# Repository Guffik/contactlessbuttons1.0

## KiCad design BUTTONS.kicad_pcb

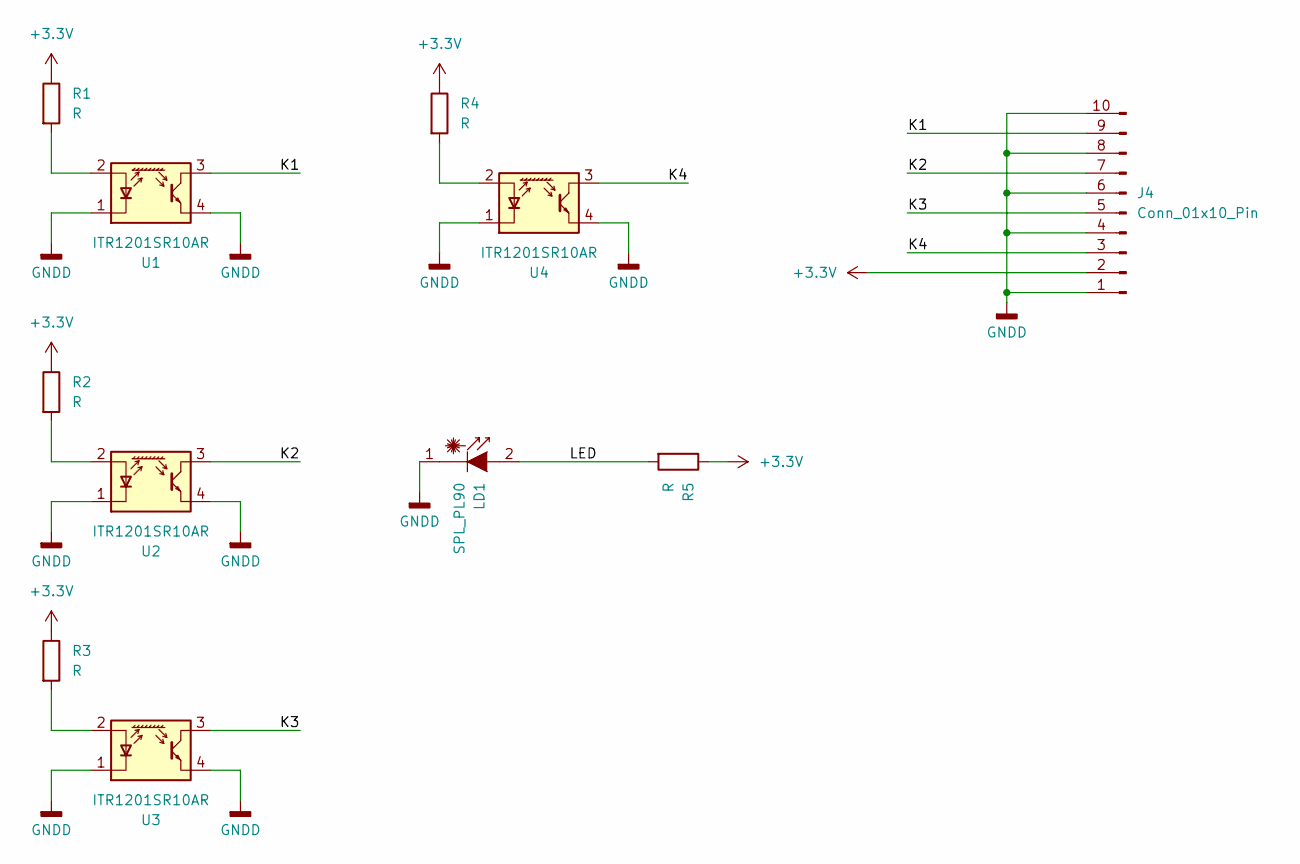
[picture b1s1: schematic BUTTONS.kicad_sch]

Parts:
J4: Conn_01x10_Pin; JST_EH_B10B-EH-A_1x10_P2.50mm_Vertical
LD1: SPL_PL90; LED_D5.0mm
R1, R2, R3, R4, R5: R; R_0603_1608Metric_Pad0.98x0.95mm_HandSolder
U1, U2, U3, U4: ITR1201SR10AR; Everlight_ITR1201SR10AR

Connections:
+3.3V: J4.2, R1.1, R2.1, R3.1, R4.1, R5.1
/K1: J4.9, U1.3
/K2: J4.7, U2.3
/K3: J4.5, U3.3
/K4: J4.3, U4.3
/LED: LD1.2 (A), R5.2
GNDD: J4.1, J4.4, J4.6, J4.8, J4.10, LD1.1 (C), U1.1 (K), U1.4, U2.1 (K), U2.4, U3.1 (K), U3.4, U4.1 (K), U4.4
unnamed: R1.2, U1.2 (A)
unnamed: R2.2, U2.2 (A)
unnamed: R3.2, U3.2 (A)
unnamed: R4.2, U4.2 (A)

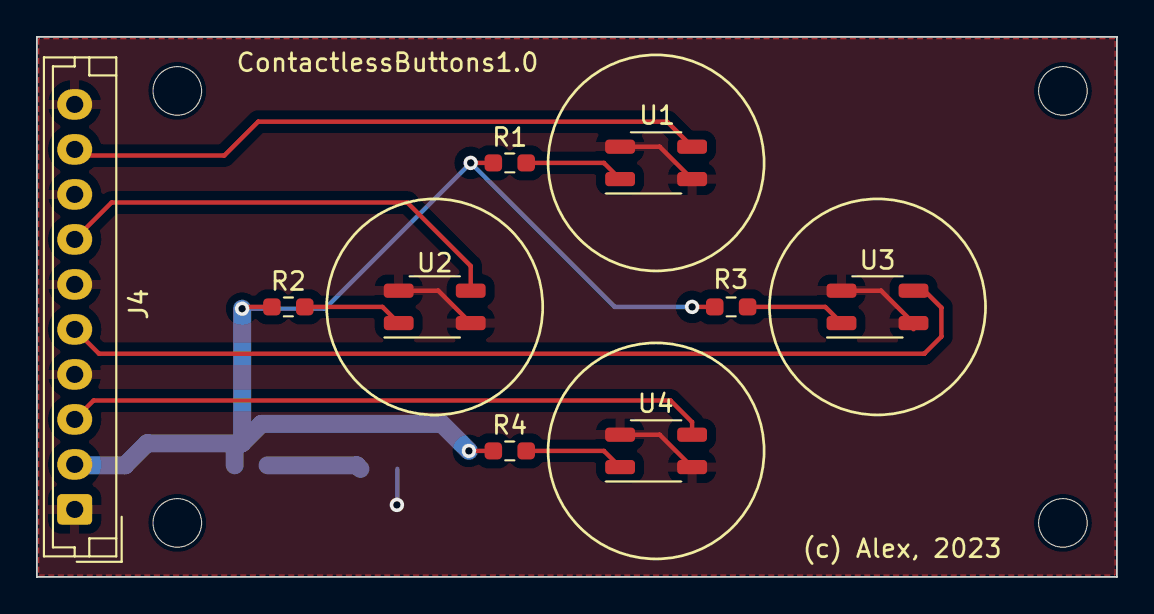
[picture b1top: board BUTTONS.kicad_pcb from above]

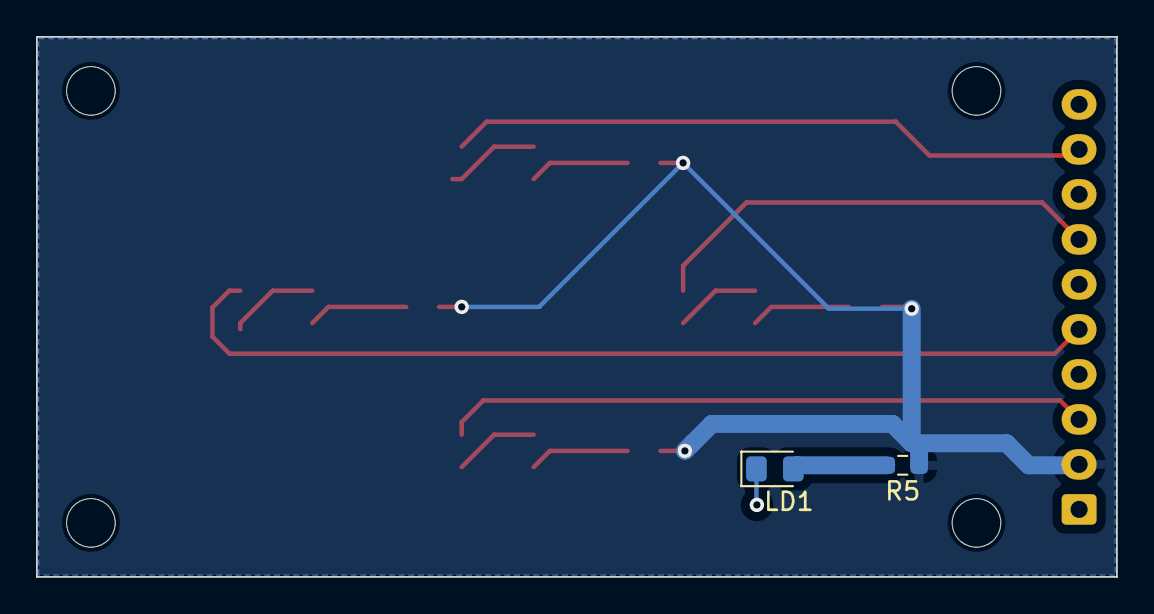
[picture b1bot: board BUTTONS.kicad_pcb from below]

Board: 2 copper layers, 60.0 x 30.0 mm, 11 parts (2 on the bottom side), 11 nets.
